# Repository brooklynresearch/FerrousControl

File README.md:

# FerrousControl
Ferrofluid controlled through an electromagnetic array

## python
This folder contains all the algorithms and code to send to the electromagnetic array.

## embedded
This folder contains all the design files and embedded code for the electromagentic controller boards.
These basically received USB Serial messages from the main computer, parse that information to the proper board, and translate those messages to the electromagnets.

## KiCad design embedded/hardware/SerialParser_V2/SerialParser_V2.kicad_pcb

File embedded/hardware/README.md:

# FerrousControl
Ferrofluid controlled through an electromagnetic array

## PCB DESIGN
Using Eagle for CAD work.  Go to folder for more information

## RASPBERRY PI CODE
To be uploaded, with any steps for set up and functionality.

## EMBEDDED CODE
TO DO

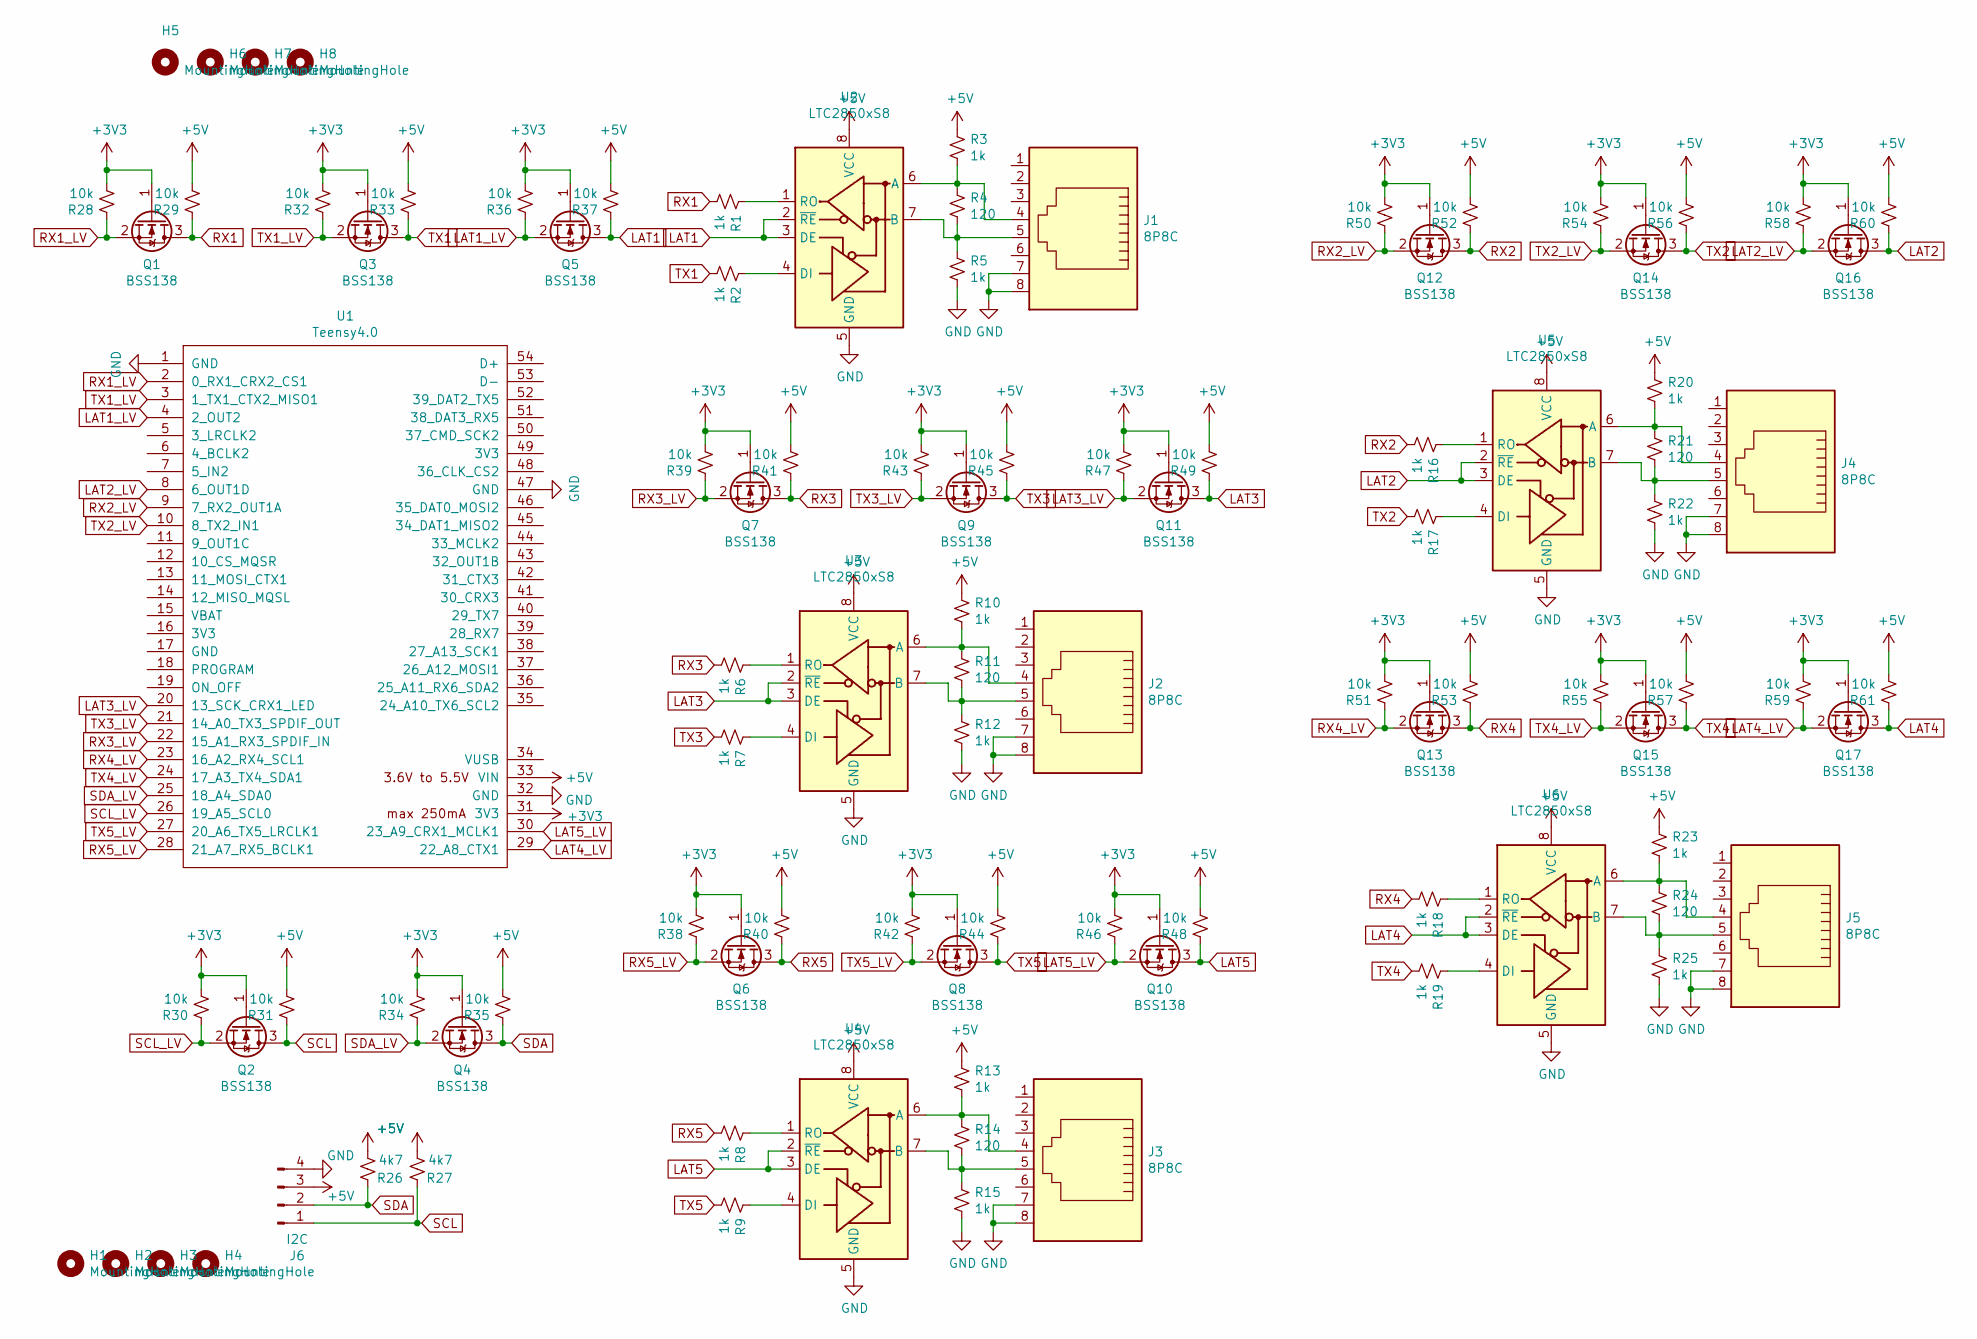
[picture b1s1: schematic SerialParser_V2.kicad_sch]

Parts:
H1, H2, H3, H4: MountingHole; MountingHole_3.2mm_M3_Pad_Via
H5, H6, H7: MountingHole; MountingHole_3.2mm_M3_ISO14580_Pad
H8: MountingHole; MountingHole_3.2mm_M3_ISO7380_Pad
J1, J2, J3, J4, J5: 8P8C; RJ45_8
J6: I2C; 4Pin_SMD_Angled_Header_2.54mm
Q1, Q2, Q3, Q4, Q5, Q6, Q7, Q8, Q9, Q10, Q11, Q12, Q13, Q14, Q15, Q16, Q17: BSS138; SOT-23
R1, R2, R3, R5, R6, R7, R8, R9, R10, R12, R13, R15, R16, R17, R18, R19, R20, R22, R23, R25: 1k; R_0603_HandSoldering
R4, R11, R14, R21, R24: 120; R_0603_HandSoldering
R26, R27: 4k7; R_0603_HandSoldering
R28, R29, R30, R31, R32, R33, R34, R35, R36, R37, R38, R39, R40, R41, R42, R43, R44, R45, R46, R47, R48, R49, R50, R51, R52, R53, R54, R55, R56, R57, R58, R59, R60, R61: 10k; R_0603_HandSoldering
U1: Teensy4.0; Teensy40
U2, U3, U4, U5, U6: LTC2850xS8; SOIC-8_3.9x4.9mm_Pitch1.27mm

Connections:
+3V3: Q1.1 (G), Q2.1 (G), Q3.1 (G), Q4.1 (G), Q5.1 (G), Q6.1 (G), Q7.1 (G), Q8.1 (G), Q9.1 (G), Q10.1 (G), Q11.1 (G), Q12.1 (G), Q13.1 (G), Q14.1 (G), Q15.1 (G), Q16.1 (G), Q17.1 (G), R28.2, R30.2, R32.2, R34.2, R36.2, R38.2, R39.2, R42.2, R43.2, R46.2, R47.2, R50.2, R51.2, R54.2, R55.2, R58.2, R59.2, U1.31 (3V3)
+5V: J6.3, R3.1, R10.1, R13.1, R20.1, R23.1, R26.2, R27.2, R29.2, R31.2, R33.2, R35.2, R37.2, R40.2, R41.2, R44.2, R45.2, R48.2, R49.2, R52.2, R53.2, R56.2, R57.2, R60.2, R61.2, U1.33 (VIN), U2.8 (VCC), U3.8 (VCC), U4.8 (VCC), U5.8 (VCC), U6.8 (VCC)
GND: J1.7, J1.8, J2.7, J2.8, J3.7, J3.8, J4.7, J4.8, J5.7, J5.8, J6.4, R5.2, R12.2, R15.2, R22.2, R25.2, U1.1 (GND), U1.32 (GND), U1.47 (GND), U2.5 (GND), U3.5 (GND), U4.5 (GND), U5.5 (GND), U6.5 (GND)
LAT1: Q5.3 (D), R37.1, U2.2 (~RE), U2.3 (DE)
LAT1_LV: Q5.2 (S), R36.1, U1.4 (2_OUT2)
LAT2: Q16.3 (D), R60.1, U5.2 (~RE), U5.3 (DE)
LAT2_LV: Q16.2 (S), R58.1, U1.8 (6_OUT1D)
LAT3: Q11.3 (D), R49.1, U3.2 (~RE), U3.3 (DE)
LAT3_LV: Q11.2 (S), R47.1, U1.20 (13_SCK_CRX1_LED)
LAT4: Q17.3 (D), R61.1, U6.2 (~RE), U6.3 (DE)
LAT4_LV: Q17.2 (S), R59.1, U1.29 (22_A8_CTX1)
LAT5: Q10.3 (D), R48.1, U4.2 (~RE), U4.3 (DE)
LAT5_LV: Q10.2 (S), R46.1, U1.30 (23_A9_CRX1_MCLK1)
unnamed: J1.4, R3.2, R4.1, U2.6 (A)
unnamed: J1.5, R4.2, R5.1, U2.7 (B)
unnamed: J2.4, R10.2, R11.1, U3.6 (A)
unnamed: J2.5, R11.2, R12.1, U3.7 (B)
unnamed: J3.4, R13.2, R14.1, U4.6 (A)
unnamed: J3.5, R14.2, R15.1, U4.7 (B)
unnamed: J4.4, R20.2, R21.1, U5.6 (A)
unnamed: J4.5, R21.2, R22.1, U5.7 (B)
unnamed: J5.4, R23.2, R24.1, U6.6 (A)
unnamed: J5.5, R24.2, R25.1, U6.7 (B)
unnamed: R1.1, U2.1 (RO)
unnamed: R2.1, U2.4 (DI)
unnamed: R6.1, U3.1 (RO)
unnamed: R7.1, U3.4 (DI)
unnamed: R8.1, U4.1 (RO)
unnamed: R9.1, U4.4 (DI)
unnamed: R16.1, U5.1 (RO)
unnamed: R17.1, U5.4 (DI)
unnamed: R18.1, U6.1 (RO)
unnamed: R19.1, U6.4 (DI)
RX1: Q1.3 (D), R1.2, R29.1
RX1_LV: Q1.2 (S), R28.1, U1.2 (0_RX1_CRX2_CS1)
RX2: Q12.3 (D), R16.2, R52.1
RX2_LV: Q12.2 (S), R50.1, U1.9 (7_RX2_OUT1A)
RX3: Q7.3 (D), R6.2, R41.1
RX3_LV: Q7.2 (S), R39.1, U1.22 (15_A1_RX3_SPDIF_IN)
RX4: Q13.3 (D), R18.2, R53.1
RX4_LV: Q13.2 (S), R51.1, U1.23 (16_A2_RX4_SCL1)
RX5: Q6.3 (D), R8.2, R40.1
RX5_LV: Q6.2 (S), R38.1, U1.28 (21_A7_RX5_BCLK1)
SCL: J6.1, Q2.3 (D), R27.1, R31.1
SCL_LV: Q2.2 (S), R30.1, U1.26 (19_A5_SCL0)
SDA: J6.2, Q4.3 (D), R26.1, R35.1
SDA_LV: Q4.2 (S), R34.1, U1.25 (18_A4_SDA0)
TX1: Q3.3 (D), R2.2, R33.1
TX1_LV: Q3.2 (S), R32.1, U1.3 (1_TX1_CTX2_MISO1)
TX2: Q14.3 (D), R17.2, R56.1
TX2_LV: Q14.2 (S), R54.1, U1.10 (8_TX2_IN1)
TX3: Q9.3 (D), R7.2, R45.1
TX3_LV: Q9.2 (S), R43.1, U1.21 (14_A0_TX3_SPDIF_OUT)
TX4: Q15.3 (D), R19.2, R57.1
TX4_LV: Q15.2 (S), R55.1, U1.24 (17_A3_TX4_SDA1)
TX5: Q8.3 (D), R9.2, R44.1
TX5_LV: Q8.2 (S), R42.1, U1.27 (20_A6_TX5_LRCLK1)

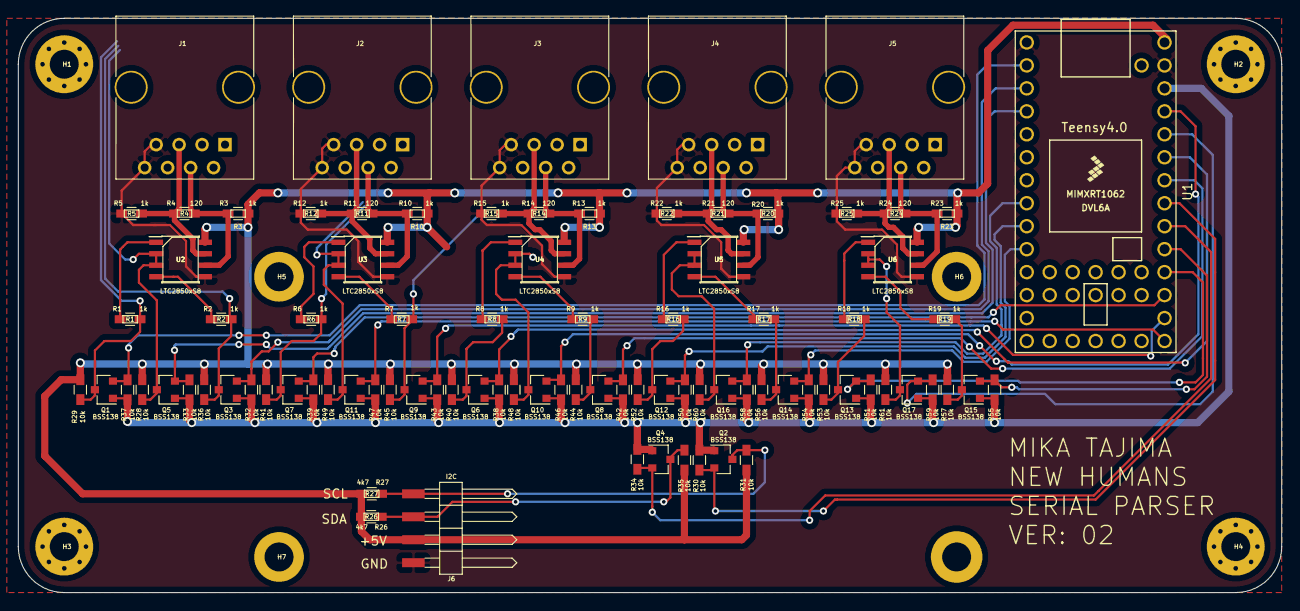
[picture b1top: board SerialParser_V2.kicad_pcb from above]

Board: 2 copper layers, 139.7 x 63.5 mm, 98 parts (0 on the bottom side), 57 nets.

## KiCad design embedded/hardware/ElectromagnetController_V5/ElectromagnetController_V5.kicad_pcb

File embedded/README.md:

# Embedded

## hardware
This folder contains the schematics and board layout files for the electromagnetic controller and the serial parser boards.

## production
This folder contains all the production files for the electromagnetic controller and serial parser boards.

## software
This folder contatins all the arduino code and libraries used for both the electromagnetic controller and serial parser boards.

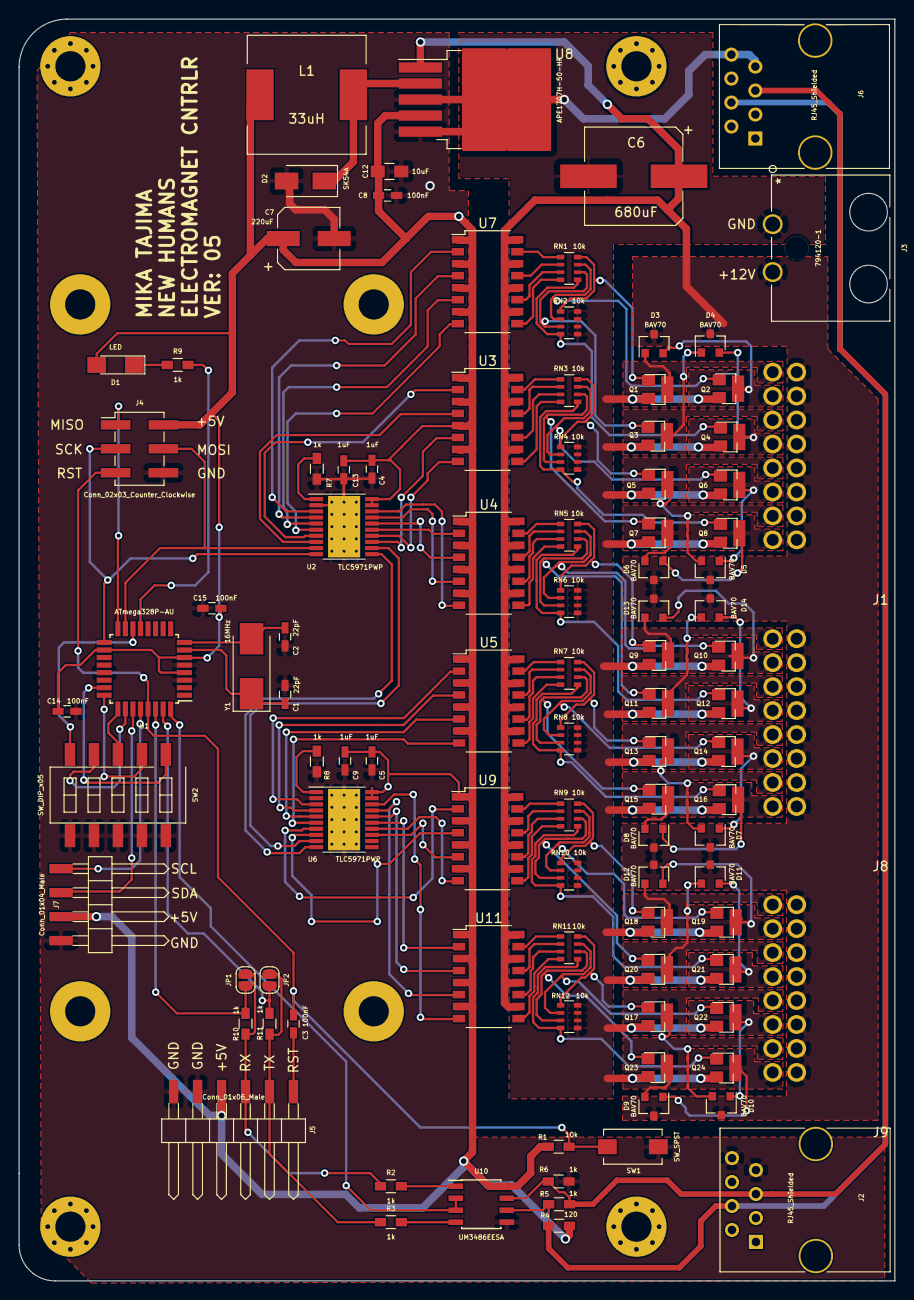
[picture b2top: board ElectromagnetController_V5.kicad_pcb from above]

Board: 2 copper layers, 92.8 x 133.8 mm, 108 parts (0 on the bottom side), 129 nets.

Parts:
C1, C2: 22pF; C_0603_HandSoldering
C3, C8, C14, C15: 100nF; C_0603_HandSoldering
C4, C5, C9, C13: 1uF; C_0603_HandSoldering
C6: 680uF; CP_Elec_10x10.5
C7: 220uF; CP_Elec_6.3x7.7
C12: 10uF; C_0805_HandSoldering
D1: LED; LED_1206_HandSoldering
D2: SK54A; D_SMA
D3, D4, D5, D6, D7, D8, D9, D10, D11, D12, D13, D14: BAV70; SOT-23
H1, H2, H3, H4: MountingHole; MountingHole_3.2mm_M3_Pad_Via
H5, H6, H7, H8: MountingHole; MountingHole_3.2mm_M3_Pad
J1, J8, J9: Conn_02x08_Odd_Even; 16Pin_8x2_Angled_Header_2.54mm
J2, J6: RJ45_Shielded; RJ45_8
J3: 794120-1
J4: Conn_02x03_Counter_Clockwise; Pin_Header_Straight_2x03_Pitch2.54mm_SMD
J5: Conn_01x06_Male; 6Pin_SMD_Angled_Header_2.54mm
J7: Conn_01x04_Male; 4Pin_SMD_Angled_Header_2.54mm
JP1, JP2: Jumper_NO_Small; SolderJumper-2_P1.3mm_Open_RoundedPad1.0x1.5mm
L1: 33uH; L_12x12mm_h8mm
Q1, Q2, Q3, Q4, Q5, Q6, Q7, Q8, Q9, Q10, Q11, Q12, Q13, Q14, Q15, Q16, Q17, Q18, Q19, Q20, Q21, Q22, Q23, Q24: Q_NMOS_GSD; SOT-23
R1: 10k; R_0603_HandSoldering
R2, R3, R4, R6, R7, R8, R9, R10, R11: 1k; R_0603_HandSoldering
R5: 120; R_0603_HandSoldering
RN1, RN2, RN3, RN4, RN5, RN6, RN7, RN8, RN9, RN10, RN11, RN12: 10k; R_Array_Convex_4x0603
SW1: SW_SPST; SW_SPST_EVQPE1
SW2: SW_DIP_x05; SW_DIP_x5_W8.61mm_Slide_LowProfile
U1: ATmega328P-AU; TQFP-32_7x7mm_Pitch0.8mm
U2, U6: TLC5971PWP; HTSSOP-20-1EP_4.4x6.5mm_Pitch0.65mm_ThermalPad
U3, U4, U5, U7, U9, U11: TLP290-4; SOP-16_4.4x10.4mm_Pitch1.27mm
U8: APE1707H-50-HF; TO-263-5_TabPin3
U10: UM3486EESA; SOIC-8_3.9x4.9mm_Pitch1.27mm
Y1: 16MHz; Crystal_SMD_0603-2pin_6.0x3.5mm_HandSoldering

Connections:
+5V: C4.1, C5.1, C7.1, C8.1, C9.1, C12.2, C13.1, C14.1, C15.1, D1.2, J4.2, J5.4, J7.3, L1.2, R1.1, R4.1, U1.4, U1.6, U1.18, U2.19, U2.20, U3.1, U3.3, U3.5, U3.7, U4.1, U4.3, U4.5, U4.7, U5.1, U5.3, U5.5, U5.7, U6.19, U6.20, U7.1, U7.3, U7.5, U7.7, U8.4, U9.1, U9.3, U9.5, U9.7, U10.8, U11.1, U11.3, U11.5, U11.7
+12V: C6.1, D3.3, D4.3, D5.3, D6.3, D7.3, D8.3, D9.3, D10.3, D11.3, D12.3, D13.3, D14.3, J1.2, J1.4, J1.6, J1.8, J1.10, J1.12, J1.14, J1.16, J3.2, J8.2, J8.4, J8.6, J8.8, J8.10, J8.12, J8.14, J8.16, J9.2, J9.4, J9.6, J9.8, J9.10, J9.12, J9.14, J9.16, U3.10, U3.12, U3.14, U3.16, U4.10, U4.12, U4.14, U4.16, U5.10, U5.12, U5.14, U5.16, U7.10, U7.12, U7.14, U7.16, U8.1, U9.10, U9.12, U9.14, U9.16, U11.10, U11.12, U11.14, U11.16
/Sheet614B2B13/EM_00: D3.1, J1.1, Q1.3
/Sheet614B2B13/EM_01: D3.2, J1.3, Q2.3
/Sheet614B2B13/EM_02: D4.1, J1.5, Q3.3
/Sheet614B2B13/EM_03: D4.2, J1.7, Q4.3
/Sheet614B2B13/EM_04: D5.2, J1.9, Q5.3
/Sheet614B2B13/EM_05: D5.1, J1.11, Q6.3
/Sheet614B2B13/EM_06: D6.2, J1.13, Q7.3
/Sheet614B2B13/EM_07: D6.1, J1.15, Q8.3
/Sheet614B2B13/EM_08: D13.1, J8.1, Q9.3
/Sheet614B2B13/EM_09: D13.2, J8.3, Q10.3
/Sheet614B2B13/EM_10: D14.1, J8.5, Q11.3
/Sheet614B2B13/EM_11: D14.2, J8.7, Q12.3
/sheet61B8751A/CLK_IN: U2.11, U6.10
/sheet61B8751A/DAT_IN: U2.12, U6.9
/sheet61B8751A/EM_12: D7.2, J8.9, Q13.3
/sheet61B8751A/EM_13: D7.1, J8.11, Q14.3
/sheet61B8751A/EM_14: D8.2, J8.13, Q15.3
/sheet61B8751A/EM_15: D8.1, J8.15, Q16.3
/sheet61B8751A/EM_16: D12.1, J9.1, Q18.3
/sheet61B8751A/EM_17: D12.2, J9.3, Q19.3
/sheet61B8751A/EM_18: D11.1, J9.5, Q20.3
/sheet61B8751A/EM_19: D11.2, J9.7, Q21.3
/sheet61B8751A/EM_20: D10.2, J9.9, Q17.3
/sheet61B8751A/EM_21: D10.1, J9.11, Q22.3
/sheet61B8751A/EM_22: D9.2, J9.13, Q23.3
/sheet61B8751A/EM_23: D9.1, J9.15, Q24.3
A: J2.4, J6.4, R4.2, R5.1, U10.6
B: J2.5, J6.5, R5.2, R6.1, U10.7
DIP0: SW2.1, U1.23
DIP1: SW2.2, U1.24
DIP2: SW2.3, U1.25
DIP3: SW2.4, U1.26
DIP4: SW2.5, U1.14
GND: C1.1, C2.1, C4.2, C5.2, C6.2, C7.2, C8.2, C9.2, C12.1, C13.2, C14.2, C15.2, D2.2, J2.7, J2.8, J3.1, J4.6, J5.5, J5.6, J6.7, J6.8, J7.4, Q1.2, Q2.2, Q3.2, Q4.2, Q5.2, Q6.2, Q7.2, Q8.2, Q9.2, Q10.2, Q11.2, Q12.2, Q13.2, Q14.2, Q15.2, Q16.2, Q17.2, Q18.2, Q19.2, Q20.2, Q21.2, Q22.2, Q23.2, Q24.2, R6.2, R7.2, R8.2, RN2.5, RN2.6, RN2.7, RN2.8, RN4.5, RN4.6, RN4.7, RN4.8, RN6.5, RN6.6, RN6.7, RN6.8, RN8.5, RN8.6, RN8.7, RN8.8, RN10.5, RN10.6, RN10.7, RN10.8, RN12.5, RN12.6, RN12.7, RN12.8, SW1.2, SW2.6, SW2.7, SW2.8, SW2.9, SW2.10, U1.3, U1.5, U1.21, U2.2, U2.21, U6.2, U6.21, U8.3, U8.5, U10.5
MISO: J4.1, U1.16
MOSI: J4.4, U1.15, U2.9
unnamed: C1.2, U1.7, Y1.1
unnamed: C2.2, U1.8, Y1.2
unnamed: C3.1, J5.1
unnamed: D1.1, R9.1
unnamed: D2.1, L1.1, U8.2
unnamed: JP1.1, R10.2, U1.30
unnamed: JP2.1, R11.2, U1.31
unnamed: Q1.1, RN1.8, RN2.1
unnamed: Q2.1, RN1.7, RN2.2
unnamed: Q3.1, RN1.6, RN2.3
unnamed: Q4.1, RN1.5, RN2.4
unnamed: Q5.1, RN3.8, RN4.1
unnamed: Q6.1, RN3.7, RN4.2
unnamed: Q7.1, RN3.6, RN4.3
unnamed: Q8.1, RN3.5, RN4.4
unnamed: Q9.1, RN5.8, RN6.1
unnamed: Q10.1, RN5.7, RN6.2
unnamed: Q11.1, RN5.6, RN6.3
unnamed: Q12.1, RN5.5, RN6.4
unnamed: Q13.1, RN7.8, RN8.1
unnamed: Q14.1, RN7.7, RN8.2
unnamed: Q15.1, RN7.6, RN8.3
unnamed: Q16.1, RN7.5, RN8.4
unnamed: Q17.1, RN11.8, RN12.1
unnamed: Q18.1, RN9.8, RN10.1
unnamed: Q19.1, RN9.7, RN10.2
unnamed: Q20.1, RN9.6, RN10.3
unnamed: Q21.1, RN9.5, RN10.4
unnamed: Q22.1, RN11.7, RN12.2
unnamed: Q23.1, RN11.6, RN12.3
unnamed: Q24.1, RN11.5, RN12.4
unnamed: R2.2, U10.1
unnamed: R3.2, U10.4
unnamed: R7.1, U2.1
unnamed: R8.1, U6.1
unnamed: R9.2, U1.13
unnamed: RN1.1, U7.15
unnamed: RN1.2, U7.13
unnamed: RN1.3, U7.11
unnamed: RN1.4, U7.9
unnamed: RN3.1, U3.15
unnamed: RN3.2, U3.13
unnamed: RN3.3, U3.11
unnamed: RN3.4, U3.9
unnamed: RN5.1, U4.15
unnamed: RN5.2, U4.13
unnamed: RN5.3, U4.11
unnamed: RN5.4, U4.9
unnamed: RN7.1, U5.15
unnamed: RN7.2, U5.13
unnamed: RN7.3, U5.11
unnamed: RN7.4, U5.9
unnamed: RN9.1, U9.15
unnamed: RN9.2, U9.13
unnamed: RN9.3, U9.11
unnamed: RN9.4, U9.9
unnamed: RN11.1, U11.15
unnamed: RN11.2, U11.13
unnamed: RN11.3, U11.11
unnamed: RN11.4, U11.9
PWM_00: U2.3, U7.2
PWM_01: U2.4, U7.4
PWM_02: U2.5, U7.6
PWM_03: U2.6, U7.8
PWM_04: U2.7, U3.2
PWM_05: U2.8, U3.4
PWM_06: U2.13, U3.6
PWM_07: U2.14, U3.8
PWM_08: U2.15, U4.2
PWM_09: U2.16, U4.4
PWM_10: U2.17, U4.6
PWM_11: U2.18, U4.8
PWM_12: U5.2, U6.3
PWM_13: U5.4, U6.4
PWM_14: U5.6, U6.5
PWM_15: U5.8, U6.6
PWM_16: U6.7, U9.2
PWM_17: U6.8, U9.4
PWM_18: U6.13, U9.6
PWM_19: U6.14, U9.8
PWM_20: U6.15, U11.2
PWM_21: U6.16, U11.4
PWM_22: U6.17, U11.6
PWM_23: U6.18, U11.8
RS485: U1.32, U10.2, U10.3
RST: C3.2, J4.5, R1.2, SW1.1, U1.29
RX: J5.3, JP1.2, R2.1, R10.1
SCK: J4.3, U1.17, U2.10
SCL: J7.1, U1.28
SDA: J7.2, U1.27
TX: J5.2, JP2.2, R3.1, R11.1

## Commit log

2019-02-05 Tester Board
    Eagle files for the intial tester board for a small electromagnetic array.
2019-02-05 Initial Tester Pictures
    Board, mount, and electromagnet pictures
2019-02-06 Updates to Preliminary Design
    Added pull down resistors for the Gate Input on the Transistors.
    All opto isolator LEDs are on the 3V3 rail
2019-02-07 Othermill Fix
    Updated layout design for othermill
2019-03-04 Serial Communication
    Basic Serial Communication between the system and magnetic array
2019-03-04 Fixed Readme
    Readme Fix
2019-07-20 Serial Communications Test
    Added Teensy Code, Arduino Code, and the current state of the python code.
2019-07-20 Serial PCBs
    Arduino Nano Serial PCB, Teensy Serial PCB, with images of schematic and layout.
2019-07-22 Serial Line Update
    Serial1.write Change
2019-07-26 320 bytes; checksum for debug
2019-07-31 Updated Teensy Code
2019-08-04 ersatz nstokes copier
    This is not necessarily helpful
2019-08-05 Teensy 3.6 Code
    Code for the Teensy 3.6
2019-08-05 temprunner
    great
2019-08-05 modified nstokes_participle for 1600 value send
    - removed previous WIP version of nstokes
    - added new nstokes_particle folder sent from Jacob
    - modified to compile data and then hand off to thread to send on serial
    - thread only receives new data from draw loop if thread is not busy
    - modified ratio function to fit within 0 to 127
    - found snake / snek function sends negative values so ratio function now zeros those out
2019-08-05 altered teensy code from one large buffer to five smaller ones split among serial
    As in title, maybe a good idea to make it pretty
2019-08-06 new amoeba logic, list reordering, serial bus baud rate changes and writes
    - amoeba directional values changes now, but will still fail eventually
    - ordering of list / bytestring sent to teensy changed to reflect message ordinance
    - serial baud rate and pin changes
2019-08-12 Added Final Arduino Code for each of the Panels
    Final Arduino Code for each of the panels.
2019-08-12 Added some comments
2019-08-12 Runs around 7 frames per second, but seems like the full test
    This version runs at around 7 frames per second, but seems to send the full complement accuratelyg
    Notes that baud rate has been increased to 2000000
2019-08-12 Switch back to 1000000 baud rate for teensy / mac
    switched back to 1000000 on Teensy-Mac comms for now in case there is legacy code out there using 10000000
2019-08-12 127 check
    safety check
2019-08-12 Infeed from test branch
    Stalls without delay from five teensies, possibly stalls here as well
2019-08-12 Ignoring .DS_Store
    Annoying
2019-08-12 fixed float issue with ratio
    ratio in non upper and lower bounds was creating floats sometimes
2019-08-13 Testing Mode Added
2019-08-13 Put safety bounds [0,127] into the testing branch
    Put this in testing branch; we need a system for keeping branches straight for stuff like this
2022-03-02 Initial Update V2
    Initial Updated Code, Schematics, and ReadMe for Version 02
2022-03-04 Updated Controller Board Defines
    Changed the Baud Rate, Commented out the BOARD_TEST, and updated the LCD to reflect the changes
2022-03-05 remove delay, fix serial port mapping
2022-03-05 test sequence working
2022-03-05 Start with test sequence
2022-03-08 fix tile mappings, other stuff
2022-03-08 add settings() function and libraries folder to make it cli-launchable
2022-03-08 swap parser positions to match board labels
2022-03-08 add readme
2022-04-05 Updates
    Changed steps (speed of snake), decay rate, framerate from 25 to 30, added var names for mode time intervals
2022-04-13 Small tweaks
2022-04-18 Zero Out Magnets without Serial
    Zero out the magnets incase we lose connection with computer or USB signal.
2022-04-24 Blooming in place
    - Some errata cleaned up
    - Some formatting changes for readability
    - Added in blooming behavior
    - Added blooming timer to trigger every three works
2022-04-25 Fullbloom update
    - short full bloom
    - extra logic for sudden off
2023-07-12 pcb, production, and software files for the embedded system
2023-07-14 reformatted python folders
2023-08-03 Added Serial Parser BOM

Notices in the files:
parts and their libraries:
Copyright 2021 Accelerated Designs. All rights reserved.
